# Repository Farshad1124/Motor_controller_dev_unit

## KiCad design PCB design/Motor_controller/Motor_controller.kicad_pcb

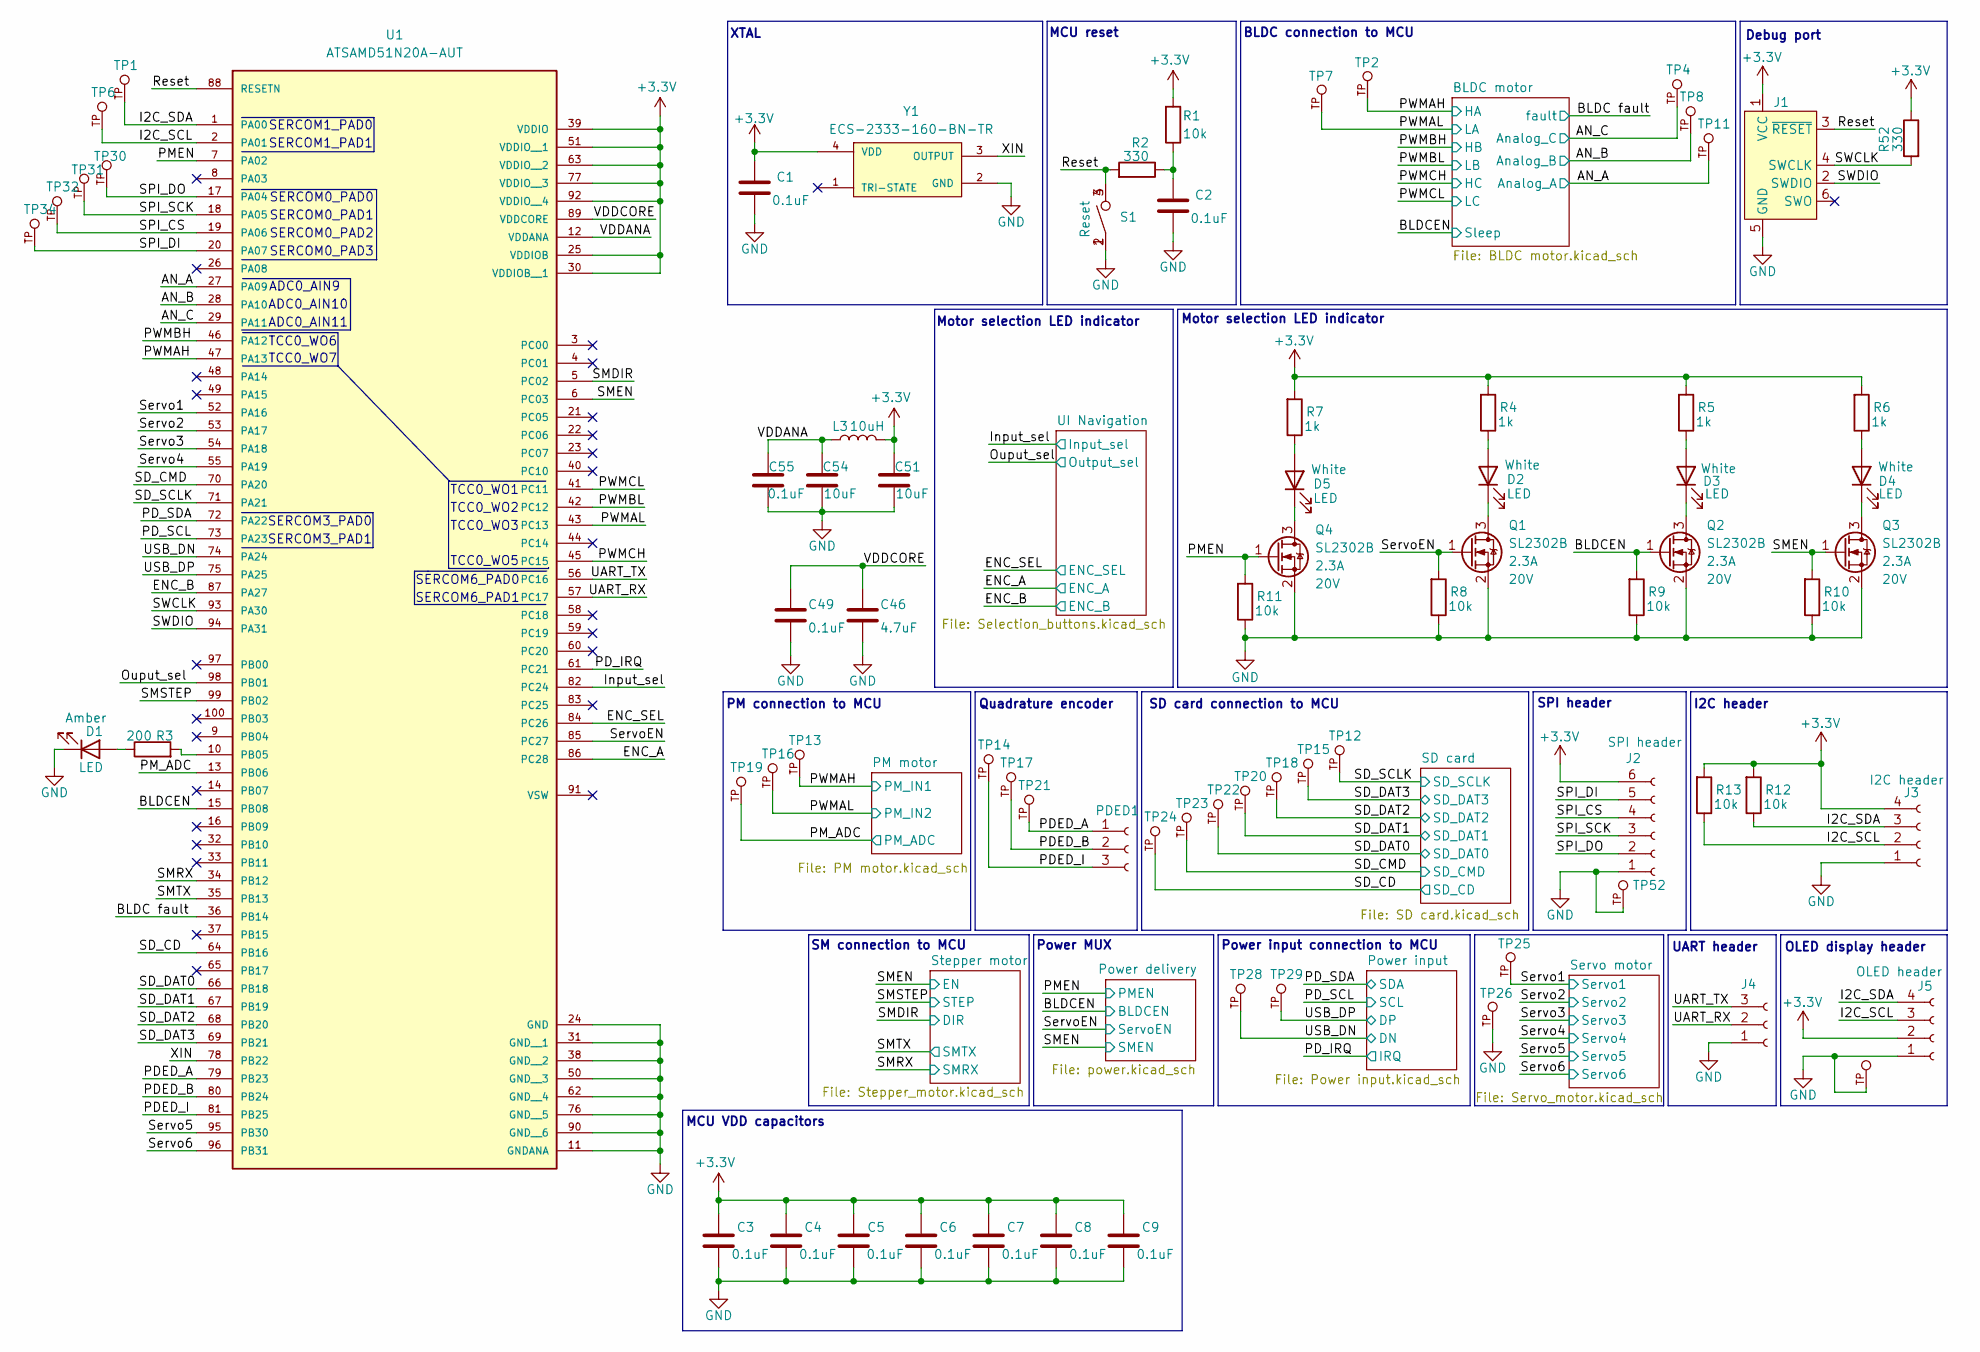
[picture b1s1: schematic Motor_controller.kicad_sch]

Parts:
C1, C2, C3, C4, C5, C6, C7, C8, C9, C49, C55: 0.1uF; C_0603_1608Metric
C46: 4.7uF; C_0603_1608Metric
C51, C54: 10uF; C_0603_1608Metric
D1, D2, D3, D4, D5: LED; LED_0603_1608Metric
J1: Conn_ARM_SWD_TagConnect_TC2030; Tag-Connect_TC2030-IDC-FP_2x03_P1.27mm_Vertical
J2: SPI header; PinSocket_1x06_P2.54mm_Vertical
J3: I2C header; PinSocket_1x04_P2.54mm_Vertical
J4: UART header; PinSocket_1x03_P2.54mm_Vertical
J5: OLED header; PinSocket_1x04_P2.54mm_Vertical
L3: 10uH; L_0805_2012Metric
PDED1: UART header; PinSocket_1x03_P2.54mm_Vertical
Q1, Q2, Q3, Q4: SL2302B; SOT23-3
R1, R8, R9, R10, R11, R12, R13: 10k; R_0603_1608Metric
R2, R52: 330; R_0603_1608Metric
R3: 200; R_0603_1608Metric
R4, R5, R6, R7: 1k; R_0603_1608Metric
S1: Reset; SMT_FS
TP1, TP2, TP4, TP6, TP7, TP8, TP11, TP12, TP13, TP14, TP15, TP16, TP17, TP18, TP19, TP20, TP21, TP22, TP23, TP24, TP25, TP26, TP27, TP28, TP29, TP30, TP31, TP32, TP34, TP52: TestPoint; KEYSTONE_1031; PARTREV B
U1: ATSAMD51N20A-AUT; QFP50P1600X1600X120-100N
Y1: ECS-2333-160-BN-TR; OSC_ECS-2333-160-BN-TR; PARTREV N/A

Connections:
+3.3V: C1.2, C3.2, C4.2, C5.2, C6.2, C7.2, C8.2, C9.2, C51.2, J1.1 (VCC), J2.6, J3.4, J5.2, L3.2, R1.1, R4.1, R5.1, R6.1, R7.1, R12.1, R13.1, R52.2, U1.25 (VDDIOB), U1.30 (VDDIOB__1), U1.39 (VDDIO), U1.51 (VDDIO__1), U1.63 (VDDIO__2), U1.77 (VDDIO__3), U1.92 (VDDIO__4), Y1.4 (VDD); also elsewhere on the board
/AN_A: TP11.TP, U1.27 (PA09); also elsewhere on the board
/AN_B: TP8.TP, U1.28 (PA10); also elsewhere on the board
/AN_C: TP4.TP, U1.29 (PA11); also elsewhere on the board
/BLDC fault: U1.36 (PB14); also elsewhere on the board
/BLDCEN: Q2.1 (G), R9.1, U1.15 (PB08); also elsewhere on the board
/ENC_A: U1.86 (PC28); also elsewhere on the board
/ENC_B: U1.87 (PA27); also elsewhere on the board
/ENC_SEL: U1.84 (PC26); also elsewhere on the board
/I2C_SCL: J3.2, J5.3, R13.2, TP6.TP, U1.2 (PA01)
/I2C_SDA: J3.3, J5.4, R12.2, TP1.TP, U1.1 (PA00)
/Input_sel: U1.82 (PC24); also elsewhere on the board
/Ouput_sel: U1.98 (PB01); also elsewhere on the board
/PDED_A: PDED1.1, TP21.TP, U1.79 (PB23)
/PDED_B: PDED1.2, TP17.TP, U1.80 (PB24)
/PDED_I: PDED1.3, TP14.TP, U1.81 (PB25)
/PD_IRQ: U1.61 (PC21); also elsewhere on the board
/PD_SCL: U1.73 (PA23); also elsewhere on the board
/PD_SDA: U1.72 (PA22); also elsewhere on the board
/PMEN: Q4.1 (G), R11.1, U1.7 (PA02); also elsewhere on the board
/PM_ADC: TP19.TP, U1.13 (PB06); also elsewhere on the board
/PWMAH: TP2.TP, TP13.TP, U1.47 (PA13); also elsewhere on the board
/PWMAL: TP7.TP, TP16.TP, U1.43 (PC13); also elsewhere on the board
/PWMBH: U1.46 (PA12); also elsewhere on the board
/PWMBL: U1.42 (PC12); also elsewhere on the board
/PWMCH: U1.45 (PC15); also elsewhere on the board
/PWMCL: U1.41 (PC11); also elsewhere on the board
/Reset: J1.3 (~RESET), R2.1, S1.3, S1.4, U1.88 (RESETN)
/SD_CD: TP24.TP, U1.64 (PB16); also elsewhere on the board
/SD_CMD: TP23.TP, U1.70 (PA20); also elsewhere on the board
/SD_DAT0: TP22.TP, U1.66 (PB18); also elsewhere on the board
/SD_DAT1: TP20.TP, U1.67 (PB19); also elsewhere on the board
/SD_DAT2: TP18.TP, U1.68 (PB20); also elsewhere on the board
/SD_DAT3: TP15.TP, U1.69 (PB21); also elsewhere on the board
/SD_SCLK: TP12.TP, U1.71 (PA21); also elsewhere on the board
/SMDIR: U1.5 (PC02); also elsewhere on the board
/SMEN: Q3.1 (G), R10.1, U1.6 (PC03); also elsewhere on the board
/SMRX: U1.34 (PB12); also elsewhere on the board
/SMSTEP: U1.99 (PB02); also elsewhere on the board
/SMTX: U1.35 (PB13); also elsewhere on the board
/SPI_CS: J2.4, TP32.TP, U1.19 (PA06)
/SPI_DI: J2.5, TP34.TP, U1.20 (PA07)
/SPI_DO: J2.2, TP30.TP, U1.17 (PA04)
/SPI_SCK: J2.3, TP31.TP, U1.18 (PA05)
/SWCLK: J1.4 (SWCLK), R52.1, U1.93 (PA30)
/SWDIO: J1.2 (SWDIO), U1.94 (PA31)
/Servo1: TP25.TP, U1.52 (PA16); also elsewhere on the board
/Servo2: U1.53 (PA17); also elsewhere on the board
/Servo3: U1.54 (PA18); also elsewhere on the board
/Servo4: U1.55 (PA19); also elsewhere on the board
/Servo5: U1.95 (PB30); also elsewhere on the board
/Servo6: U1.96 (PB31); also elsewhere on the board
/ServoEN: Q1.1 (G), R8.1, U1.85 (PC27); also elsewhere on the board
/UART_RX: J4.2, U1.57 (PC17)
/UART_TX: J4.3, U1.56 (PC16)
/USB_DN: TP28.TP, U1.74 (PA24); also elsewhere on the board
/USB_DP: TP29.TP, U1.75 (PA25); also elsewhere on the board
/VDDANA: C54.2, C55.2, L3.1, U1.12 (VDDANA)
/VDDCORE: C46.2, C49.2, U1.89 (VDDCORE)
/XIN: U1.78 (PB22), Y1.3 (OUTPUT)
GND: C1.1, C2.1, C3.1, C4.1, C5.1, C6.1, C7.1, C8.1, C9.1, C46.1, C49.1, C51.1, C54.1, C55.1, D1.1 (K), J1.5 (GND), J2.1, J3.1, J4.1, J5.1, Q1.2 (S), Q2.2 (S), Q3.2 (S), Q4.2 (S), R8.2, R9.2, R10.2, R11.2, S1.1, S1.2, TP26.TP, TP27.TP, TP52.TP, U1.11 (GNDANA), U1.24 (GND), U1.31 (GND__1), U1.38 (GND__2), U1.50 (GND__3), U1.62 (GND__4), U1.76 (GND__5), U1.90 (GND__6), Y1.2 (GND); also elsewhere on the board
unnamed: C2.2, R1.2, R2.2
unnamed: D1.2 (A), R3.2
unnamed: D2.2 (A), R4.2
unnamed: D2.1 (K), Q1.3 (D)
unnamed: D3.2 (A), R5.2
unnamed: D3.1 (K), Q2.3 (D)
unnamed: D4.2 (A), R6.2
unnamed: D4.1 (K), Q3.3 (D)
unnamed: D5.2 (A), R7.2
unnamed: D5.1 (K), Q4.3 (D)
unnamed: R3.1, U1.10 (PB05)

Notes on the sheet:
Quadrature encoder
OLED display header
SERCOM6_PAD1
Motor selection LED indicator
Power MUX
SERCOM1_PAD1
TCC0_WO6
SERCOM0_PAD2
TCC0_WO7
I2C header
Debug port
SM connection to MCU
SD card connection to MCU
ADC0_AIN9
SERCOM3_PAD0
SERCOM0_PAD0
SERCOM1_PAD0
MCU VDD capacitors
MCU reset
ADC0_AIN11
UART header
PM connection to MCU
SERCOM0_PAD3
XTAL
Power input connection to MCU
ADC0_AIN10
TCC0_WO3
TCC0_WO1
TCC0_WO5
BLDC connection to MCU
SERCOM3_PAD1
SERCOM0_PAD1
SPI header
TCC0_WO2
SERCOM6_PAD0

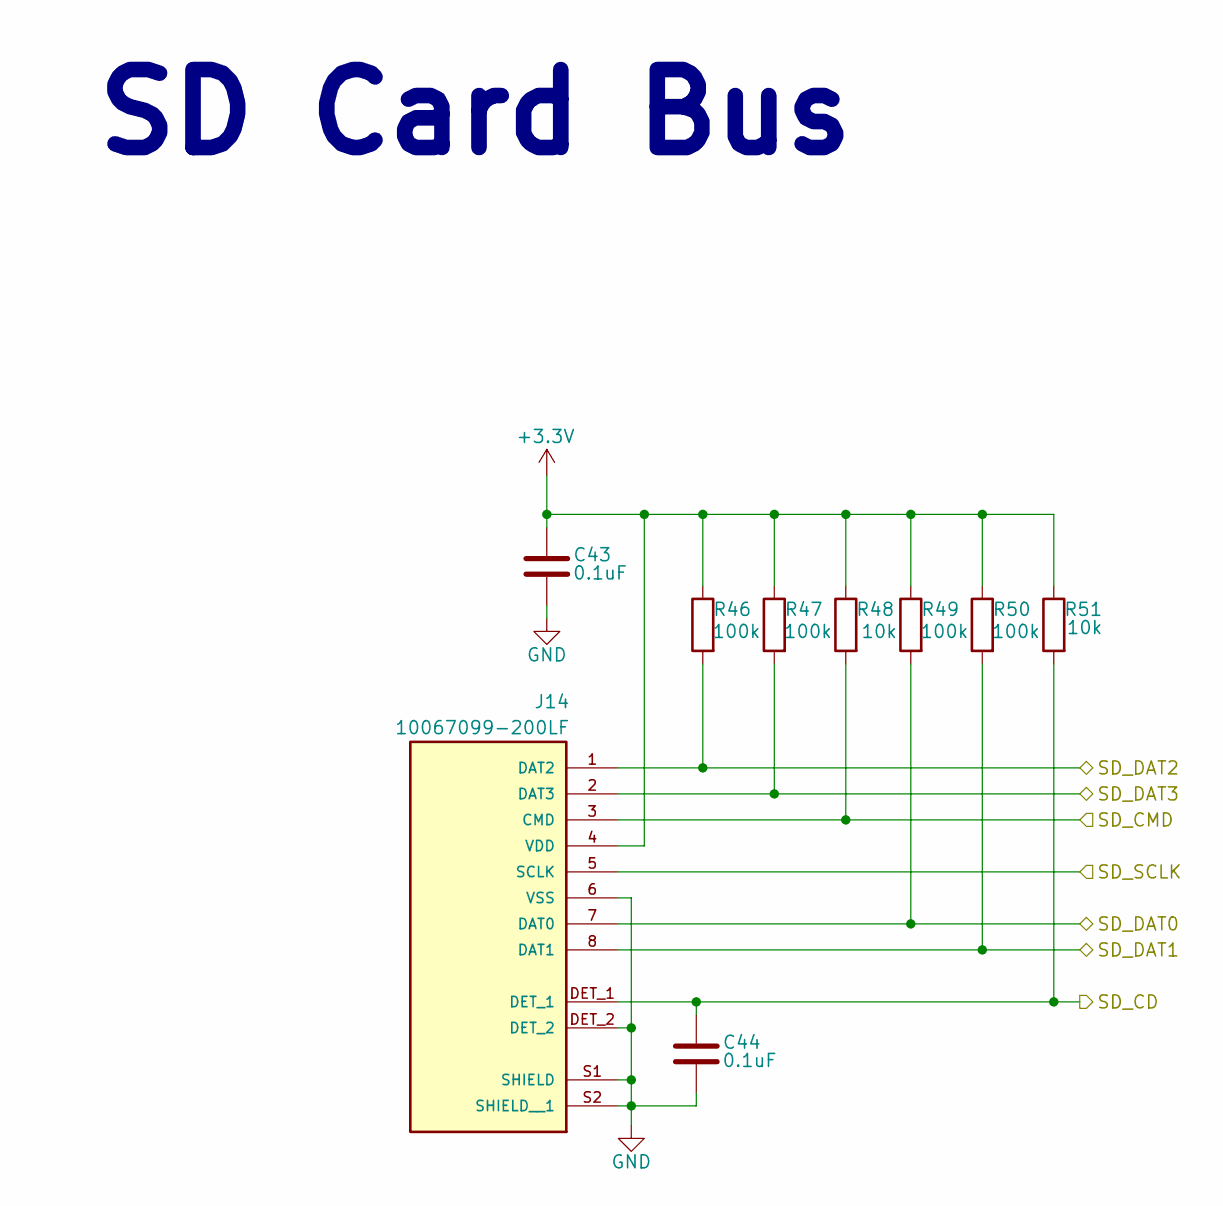
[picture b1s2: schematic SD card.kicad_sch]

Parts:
C43, C44: 0.1uF; C_0603_1608Metric
J14: 10067099-200LF; AMPHENOL_10067099-200LF; PARTREV H
R46, R47, R49, R50: 100k; R_0603_1608Metric
R48, R51: 10k; R_0603_1608Metric

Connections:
+3.3V: C43.2, J14.4 (VDD), R46.2, R47.2, R48.2, R49.2, R50.2, R51.2; also elsewhere on the board
/SD_CD: C44.2, J14.DET_1, R51.1; also elsewhere on the board
/SD_CMD: J14.3 (CMD), R48.1; also elsewhere on the board
/SD_DAT0: J14.7 (DAT0), R49.1; also elsewhere on the board
/SD_DAT1: J14.8 (DAT1), R50.1; also elsewhere on the board
/SD_DAT2: J14.1 (DAT2), R46.1; also elsewhere on the board
/SD_DAT3: J14.2 (DAT3), R47.1; also elsewhere on the board
/SD_SCLK: J14.5 (SCLK); also elsewhere on the board
GND: C43.1, C44.1, J14.6 (VSS), J14.DET_2, J14.S1 (SHIELD), J14.S2 (SHIELD__1); also elsewhere on the board

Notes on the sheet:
SD Card Bus

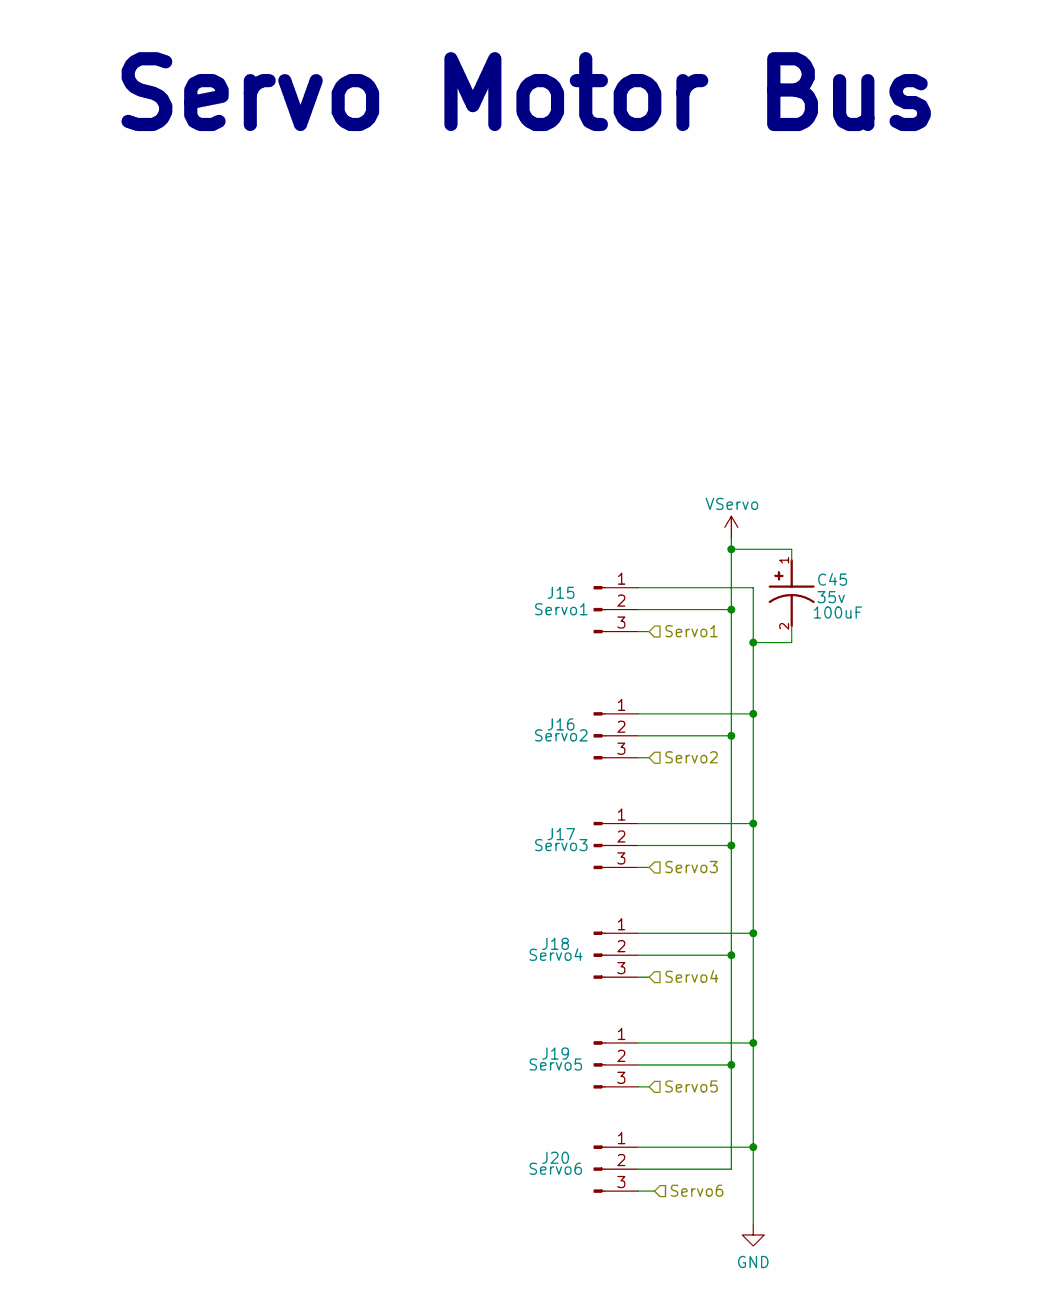
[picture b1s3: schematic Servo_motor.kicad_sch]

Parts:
C45: 100uF; CAPAE660X600N; voltage 35v
J15: Servo1; PinHeader_1x03_P2.54mm_Vertical
J16: Servo2; PinHeader_1x03_P2.54mm_Vertical
J17: Servo3; PinHeader_1x03_P2.54mm_Vertical
J18: Servo4; PinHeader_1x03_P2.54mm_Vertical
J19: Servo5; PinHeader_1x03_P2.54mm_Vertical
J20: Servo6; PinHeader_1x03_P2.54mm_Vertical

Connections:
/Servo1: J15.3; also elsewhere on the board
/Servo2: J16.3; also elsewhere on the board
/Servo3: J17.3; also elsewhere on the board
/Servo4: J18.3; also elsewhere on the board
/Servo5: J19.3; also elsewhere on the board
/Servo6: J20.3; also elsewhere on the board
GND: C45.2, J15.1, J16.1, J17.1, J18.1, J19.1, J20.1; also elsewhere on the board
VServo: C45.1, J15.2, J16.2, J17.2, J18.2, J19.2, J20.2; also elsewhere on the board

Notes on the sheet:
Servo Motor Bus

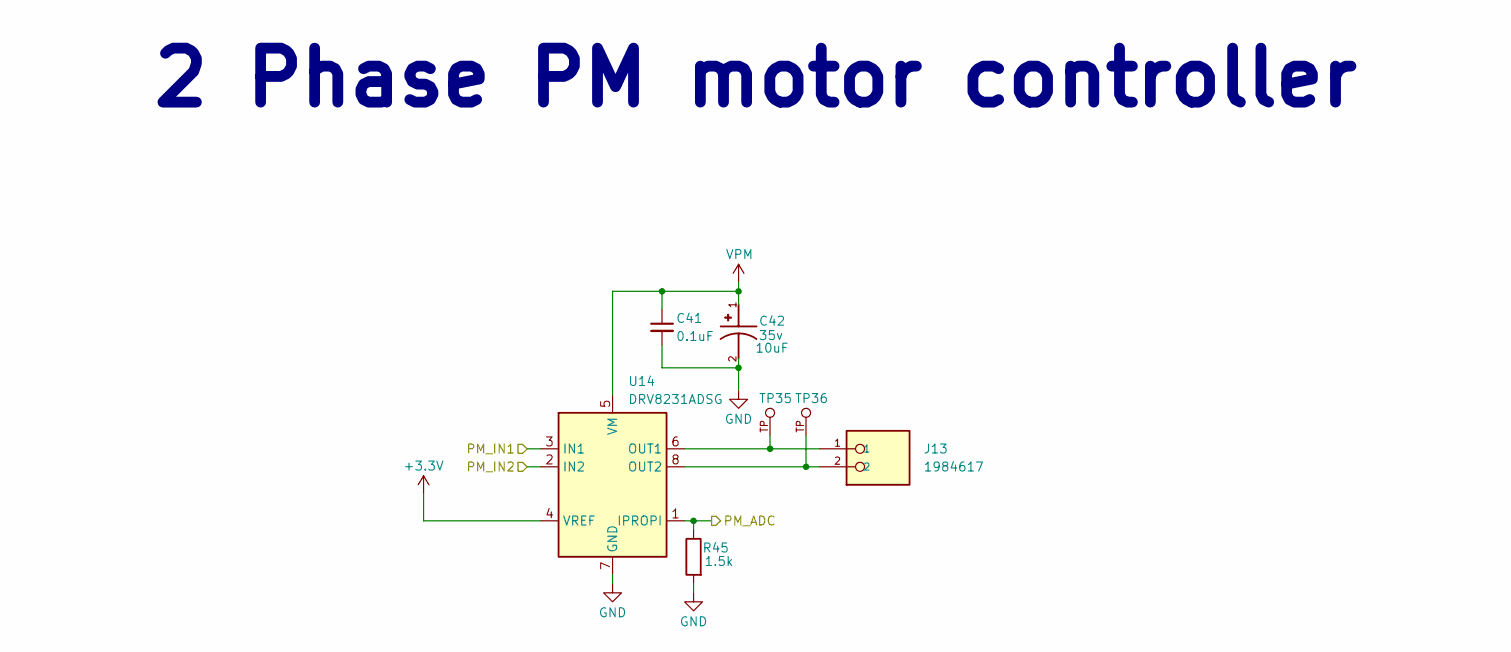
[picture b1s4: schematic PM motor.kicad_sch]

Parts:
C41: 0.1uF; C_0603_1608Metric; voltage 50v
C42: 10uF; CAPAE660X600N; voltage 35v
J13: 1984617; PHOENIX_1984617; PARTREV 22.08.2018
R45: 1.5k; R_0603_1608Metric
TP35, TP36: TestPoint; KEYSTONE_1031; PARTREV B
U14: DRV8231ADSG; WSON8_DSG_TEX

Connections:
+3.3V: U14.4 (VREF); also elsewhere on the board
/PM_ADC: R45.2, U14.1 (IPROPI); also elsewhere on the board
/PWMAH: U14.3 (IN1); also elsewhere on the board
/PWMAL: U14.2 (IN2); also elsewhere on the board
GND: C41.2, C42.2, R45.1, U14.7 (GND), U14.9 (GND); also elsewhere on the board
unnamed: J13.1, TP35.TP, U14.6 (OUT1)
unnamed: J13.2, TP36.TP, U14.8 (OUT2)
VPM: C41.1, C42.1, U14.5 (VM); also elsewhere on the board

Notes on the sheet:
2 Phase PM motor controller

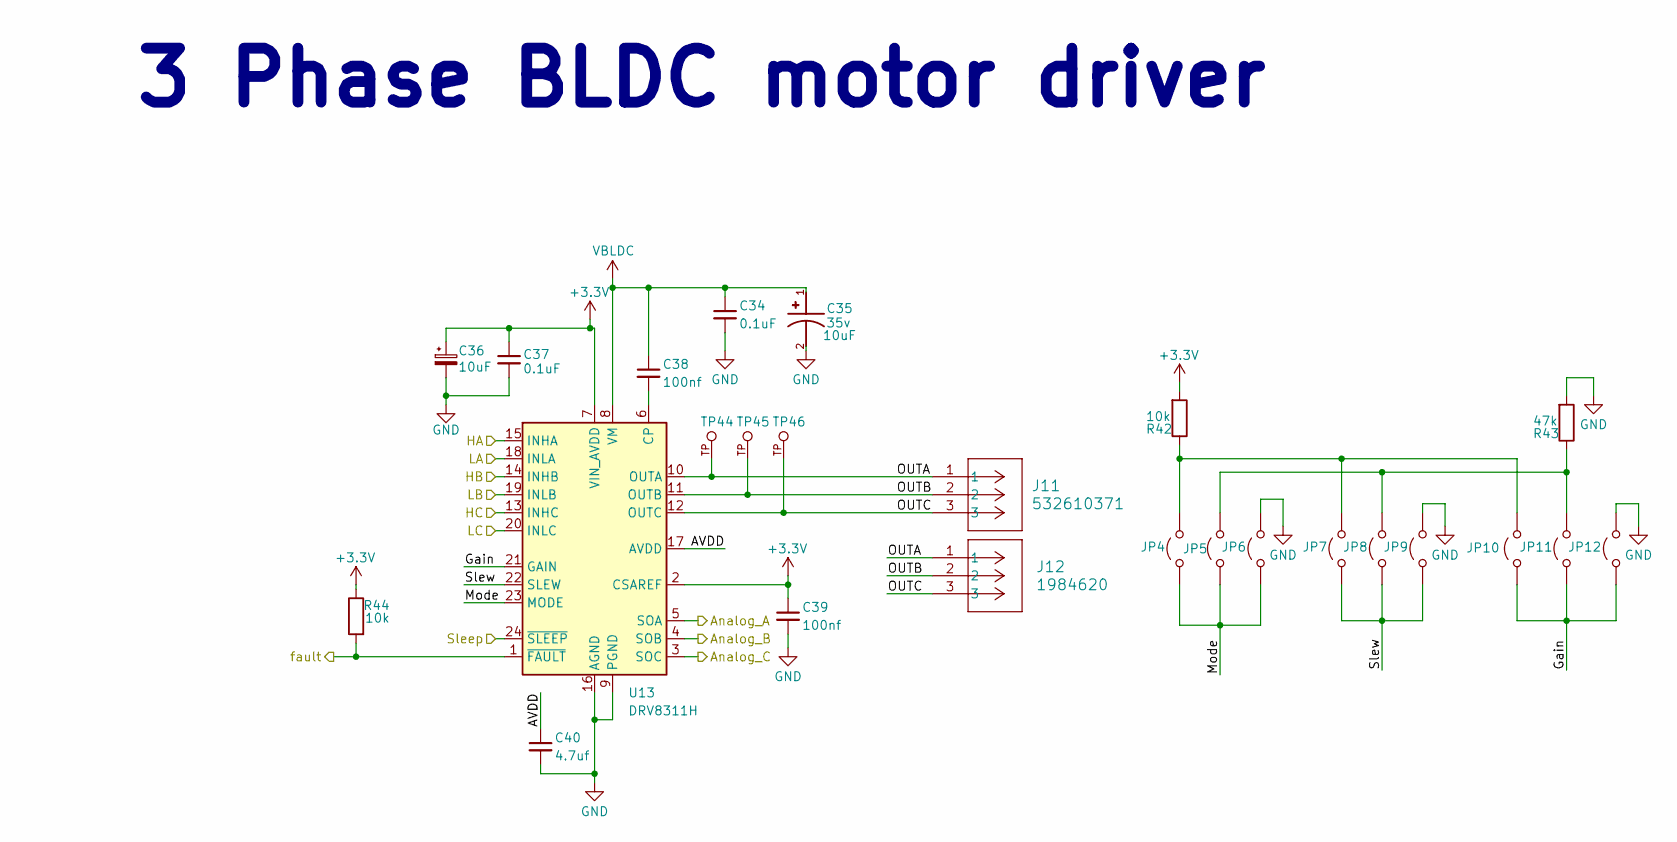
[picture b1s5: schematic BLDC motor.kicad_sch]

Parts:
C34, C37: 0.1uF; C_0603_1608Metric
C35: 10uF; CAPAE660X600N; voltage 35v
C36: 10uF; CP_EIA-2012-12_Kemet-R
C38, C39: 100nf; C_0603_1608Metric; voltage 50v
C40: 4.7uf; C_0603_1608Metric
J11: 532610371; CONN_532610001-SD_03_MOL
J12: 1984620; CONN_1984620_PXC
JP4, JP5, JP6, JP7, JP8, JP9, JP10, JP11, JP12: NPC02SXON-RC; TestPoint_2Pads_Pitch2.54mm_Drill0.8mm
R42, R44: 10k; R_0603_1608Metric
R43: 47k; R_0603_1608Metric
TP44, TP45, TP46: TestPoint; KEYSTONE_1031; PARTREV B
U13: DRV8311H; Texas_RRW0024A_WQFN-24-1EP_3x3mm_P0.4mm_EP1.9x1.9mm_Thermal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

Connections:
+3.3V: C36.1, C37.1, C39.1, R42.1, R44.2, U13.2 (CSAREF), U13.7 (VIN_AVDD); also elsewhere on the board
/AN_A: U13.5 (SOA); also elsewhere on the board
/AN_B: U13.4 (SOB); also elsewhere on the board
/AN_C: U13.3 (SOC); also elsewhere on the board
/BLDC fault: R44.1, U13.1 (~FAULT); also elsewhere on the board
/BLDC motor/AVDD: C40.1, U13.17 (AVDD)
/BLDC motor/Gain: JP10.1 (A), JP11.1 (A), JP12.1 (A), U13.21 (GAIN)
/BLDC motor/Mode: JP4.1 (A), JP5.1 (A), JP6.1 (A), U13.23 (MODE)
/BLDC motor/OUTA: J11.1, J12.1, TP44.TP, U13.10 (OUTA)
/BLDC motor/OUTB: J11.2, J12.2, TP45.TP, U13.11 (OUTB)
/BLDC motor/OUTC: J11.3, J12.3, TP46.TP, U13.12 (OUTC)
/BLDC motor/Slew: JP7.1 (A), JP8.1 (A), JP9.1 (A), U13.22 (SLEW)
/BLDCEN: U13.24 (~SLEEP); also elsewhere on the board
/PWMAH: U13.15 (INHA); also elsewhere on the board
/PWMAL: U13.18 (INLA); also elsewhere on the board
/PWMBH: U13.14 (INHB); also elsewhere on the board
/PWMBL: U13.19 (INLB); also elsewhere on the board
/PWMCH: U13.13 (INHC); also elsewhere on the board
/PWMCL: U13.20 (INLC); also elsewhere on the board
GND: C34.2, C35.2, C36.2, C37.2, C39.2, C40.2, JP6.2 (B), JP9.2 (B), JP12.2 (B), R43.1, U13.9 (PGND), U13.16 (AGND), U13.25 (PGND); also elsewhere on the board
unnamed: JP4.2 (B), JP7.2 (B), JP10.2 (B), R42.2
unnamed: JP5.2 (B), JP8.2 (B), JP11.2 (B), R43.2
unnamed: C38.2, U13.6 (CP)
VBLDC: C34.1, C35.1, C38.1, U13.8 (VM); also elsewhere on the board

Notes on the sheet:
3 Phase BLDC motor driver

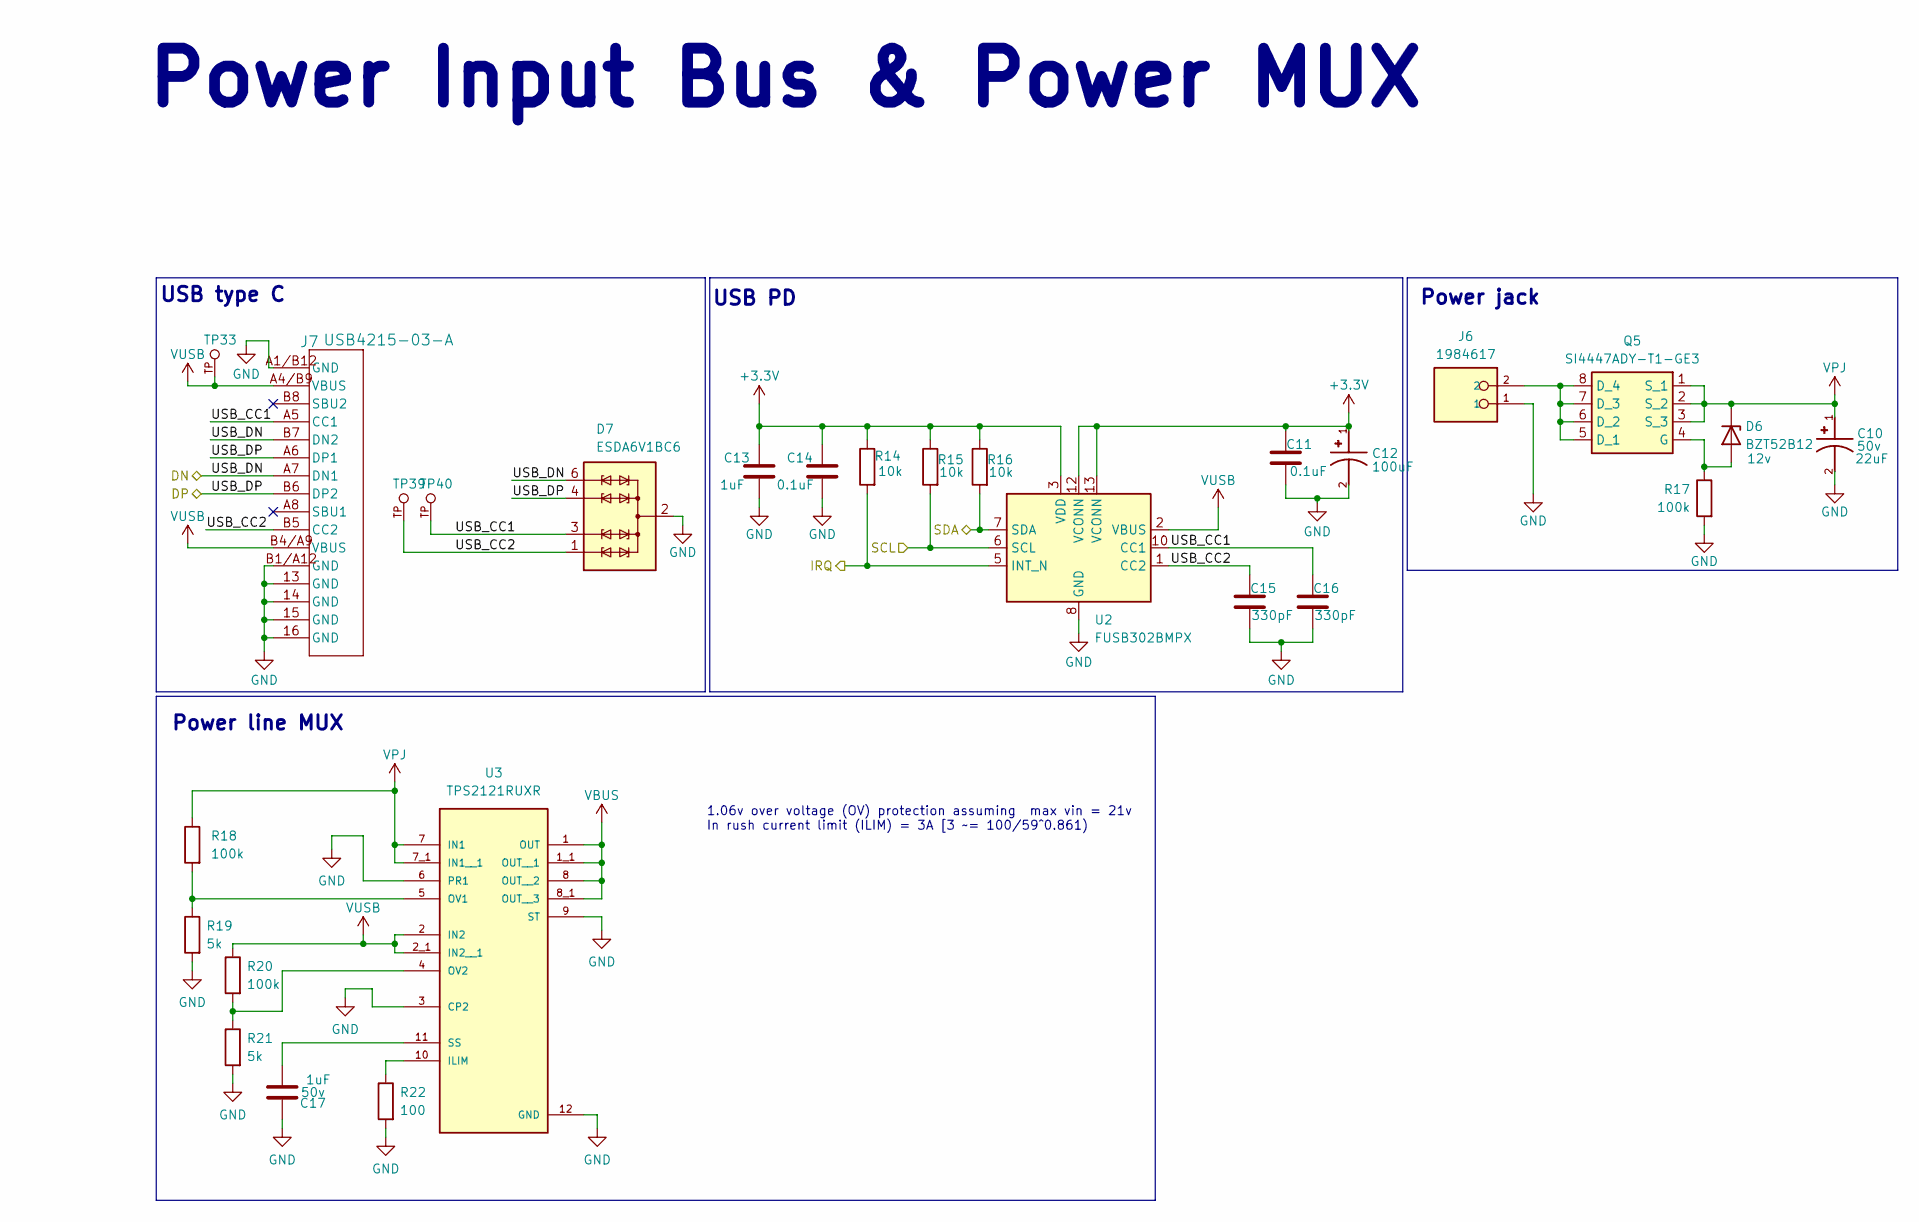
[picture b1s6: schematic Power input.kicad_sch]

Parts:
C10: 22uF; CAPAE660X600N; voltage 50v
C11, C14: 0.1uF; C_0603_1608Metric
C12: 100uF; CP_EIA-3528-12_Kemet-T; voltage 50v
C13: 1uF; C_0603_1608Metric
C15, C16: 330pF; C_0603_1608Metric
C17: 1uF; C_0603_1608Metric; Voltage 50v
D6: BZT52B12; D_SOD-123; voltage 12v
D7: ESDA6V1BC6; SOT-23-6
J6: 1984617; PHOENIX_1984617; PARTREV 22.08.2018
J7: USB4215-03-A; USBC_CONN_8p94X6p5X3p16_12L_GCC
Q5: SI4447ADY-T1-GE3; SOIC127P600X175-8N; Mouser Part Number 78-SI4447ADY-T1-GE3
R14, R15, R16: 10k; R_0603_1608Metric
R17, R18, R20: 100k; R_0603_1608Metric
R19, R21: 5k; R_0603_1608Metric
R22: 100; R_0603_1608Metric
TP33, TP39, TP40: TestPoint; KEYSTONE_1031; PARTREV B
U2: FUSB302BMPX; WQFN-14-1EP_2.5x2.5mm_P0.5mm_EP1.45x1.45mm
U3: TPS2121RUXR; IC_TPS2121RUXR

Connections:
+3.3V: C11.2, C12.1, C13.2, C14.2, R14.2, R15.2, R16.2, U2.3 (VDD), U2.4 (VDD), U2.12 (VCONN), U2.13 (VCONN); also elsewhere on the board
/PD_IRQ: R14.1, U2.5 (INT_N); also elsewhere on the board
/PD_SCL: R15.1, U2.6 (SCL); also elsewhere on the board
/PD_SDA: R16.1, U2.7 (SDA); also elsewhere on the board
/Power input/USB_CC1: C16.2, D7.3 (TVS2), J7.A5 (CC1), TP40.TP, U2.10 (CC1), U2.11 (CC1)
/Power input/USB_CC2: C15.2, D7.1 (TVS1), J7.B5 (CC2), TP39.TP, U2.1 (CC2), U2.14 (CC2)
/USB_DN: D7.6 (TVS4), J7.A7 (DN1), J7.B7 (DN2); also elsewhere on the board
/USB_DP: D7.4 (TVS3), J7.A6 (DP1), J7.B6 (DP2); also elsewhere on the board
GND: C10.2, C11.1, C12.2, C13.1, C14.1, C15.1, C16.1, C17.2, D7.2 (COM), D7.5 (COM), J6.1, J7.13 (GND), J7.14 (GND), J7.15 (GND), J7.16 (GND), J7.A1/B12 (GND), J7.B1/A12 (GND), R17.2, R19.2, R21.2, R22.2, U2.8 (GND), U2.9 (GND), U2.15 (GND), U3.3 (CP2), U3.6 (PR1), U3.9 (ST), U3.12 (GND); also elsewhere on the board
unnamed: D6.2 (A), Q5.4 (G), R17.1
unnamed: J6.2, Q5.5 (D_1), Q5.6 (D_2), Q5.7 (D_3), Q5.8 (D_4)
unnamed: R22.1, U3.10 (ILIM)
unnamed: R18.2, R19.1, U3.5 (OV1)
unnamed: R20.2, R21.1, U3.4 (OV2)
unnamed: C17.1, U3.11 (SS)
VBUS: U3.1 (OUT), U3.1_1 (OUT__1), U3.8 (OUT__2), U3.8_1 (OUT__3); also elsewhere on the board
VPJ: C10.1, D6.1 (K), Q5.1 (S_1), Q5.2 (S_2), Q5.3 (S_3), R18.1, U3.7 (IN1), U3.7_1 (IN1__1)
VUSB: J7.A4/B9 (VBUS), J7.B4/A9 (VBUS), R20.1, TP33.TP, U2.2 (VBUS), U3.2 (IN2), U3.2_1 (IN2__1)

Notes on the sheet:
Power Input Bus & Power MUX
USB PD
USB type C
Power line MUX
1.06v over voltage (OV) protection assuming max vin = 21v In rush current limit (ILIM) = 3A [3 ~= 100/59^0.861)
Power jack

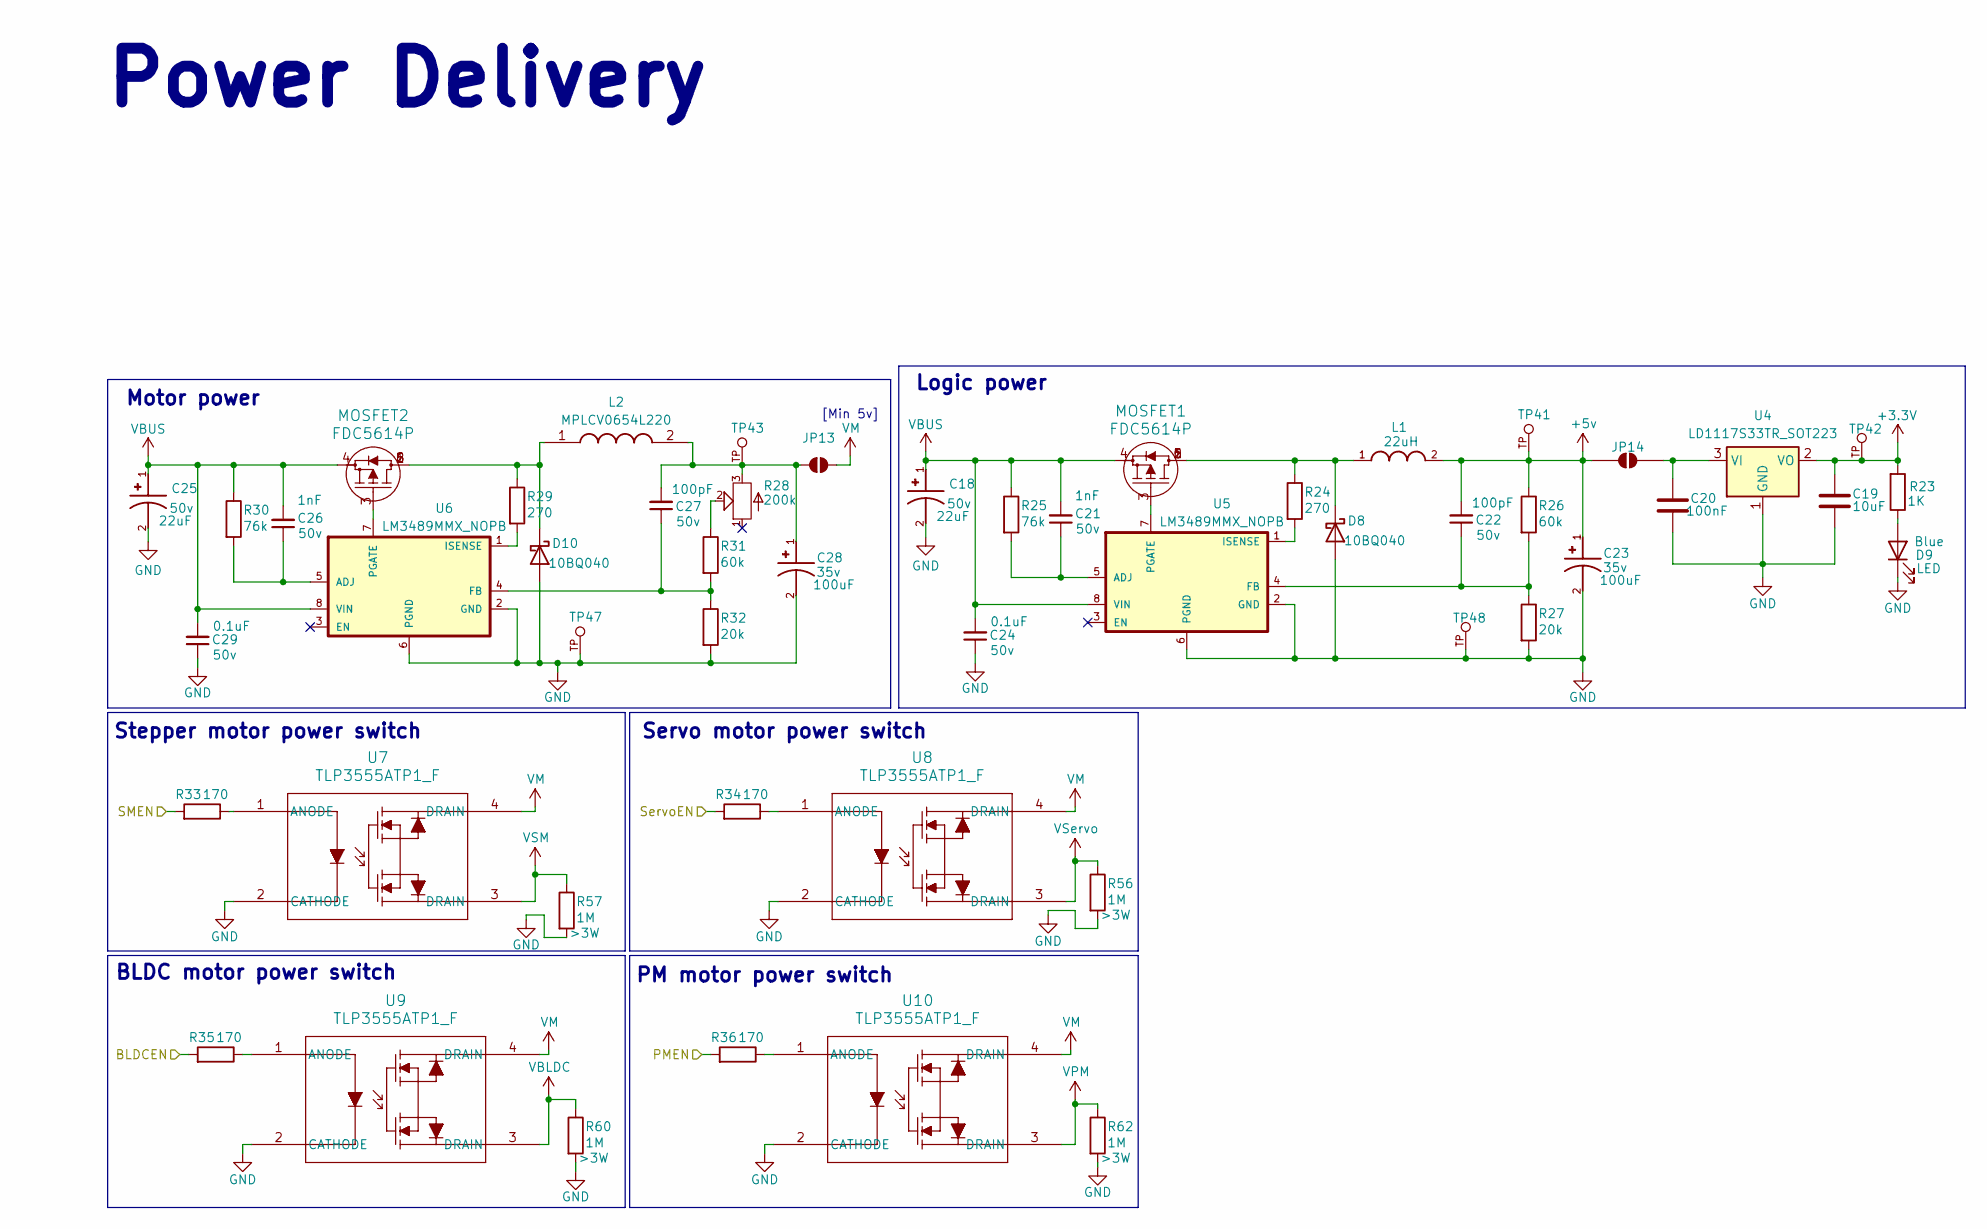
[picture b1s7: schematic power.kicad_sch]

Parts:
C18, C25: 22uF; CAPAE660X600N; voltage 50v
C19: 10uF; C_0603_1608Metric
C20: 100nF; C_0603_1608Metric
C21, C26: 1nF; C_0603_1608Metric; Voltage 50v
C22, C27: 100pF; C_0603_1608Metric; Voltage 50v
C23, C28: 100uF; CAPAE660X600N; voltage 35v
C24, C29: 0.1uF; C_0603_1608Metric; Voltage 50v
D8, D10: 10BQ040; D_SMB
D9: LED; LED_0603_1608Metric
JP13: Jumper_2_NO
JP14: SolderJumper_2_Open; SolderJumper-2_P1.3mm_Open_RoundedPad1.0x1.5mm
L1: 22uH; IND_VLS6045EX-220M
L2: MPLCV0654L220; INDPM7967X540N; Mouser Part Number 80-MPLCV0654L220
MOSFET1, MOSFET2: FDC5614P; TSOT23-6_419BL_ONS
R23: 1K; R_0603_1608Metric
R24, R29: 270; R_0603_1608Metric
R25, R30: 76k; R_0603_1608Metric
R26, R31: 60k; R_0603_1608Metric
R27, R32: 20k; R_0603_1608Metric
R28: 200k; TRIM_TC33X-2-204E
R33, R34, R35, R36: 170; R_0603_1608Metric
R56, R57, R60, R62: 1M; R_1206_3216Metric
TP41, TP42, TP43, TP47, TP48: TestPoint; KEYSTONE_1031; PARTREV B
U4: LD1117S33TR_SOT223; SOT-223-3_TabPin2
U5, U6: LM3489MMX_NOPB; SOP65P490X110-8N
U7, U8, U9, U10: TLP3555ATP1_F; 11-5B201S_TOS

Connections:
+3.3V: C19.2, R23.1, TP42.TP, U4.2 (VO); also elsewhere on the board
+5v: C22.2, C23.1, JP14.2 (B), L1.2, R26.1, TP41.TP
/BLDCEN: R35.1; also elsewhere on the board
/PMEN: R36.1; also elsewhere on the board
/SMEN: R33.1; also elsewhere on the board
/ServoEN: R34.1; also elsewhere on the board
GND: C18.2, C19.1, C20.1, C23.2, C24.1, C25.2, C28.2, C29.1, D8.2 (A), D9.1 (K), D10.2 (A), R27.2, R32.2, R56.2, R57.2, R60.2, R62.2, TP47.TP, TP48.TP, U4.1 (GND), U5.2 (GND), U5.6 (PGND), U6.2 (GND), U6.6 (PGND), U7.2 (CATHODE), U8.2 (CATHODE), U9.2 (CATHODE), U10.2 (CATHODE); also elsewhere on the board
unnamed: D8.1 (K), L1.1, MOSFET1.1, MOSFET1.2, MOSFET1.5, MOSFET1.6, R24.1
unnamed: D9.2 (A), R23.2
unnamed: D10.1 (K), L2.1, MOSFET2.1, MOSFET2.2, MOSFET2.5, MOSFET2.6, R29.1
unnamed: C27.2, C28.1, JP13.2 (B), L2.2, R28.3, TP43.TP
unnamed: C20.2, JP14.1 (A), U4.3 (VI)
unnamed: R28.2, R31.1
unnamed: C21.1, R25.2, U5.5 (ADJ)
unnamed: C22.1, R26.2, R27.1, U5.4 (FB)
unnamed: R24.2, U5.1 (ISENSE)
unnamed: MOSFET1.3, U5.7 (PGATE)
unnamed: C26.1, R30.2, U6.5 (ADJ)
unnamed: C27.1, R31.2, R32.1, U6.4 (FB)
unnamed: R29.2, U6.1 (ISENSE)
unnamed: MOSFET2.3, U6.7 (PGATE)
unnamed: R33.2, U7.1 (ANODE)
unnamed: R34.2, U8.1 (ANODE)
unnamed: R35.2, U9.1 (ANODE)
unnamed: R36.2, U10.1 (ANODE)
VBLDC: R60.1, U9.3 (DRAIN); also elsewhere on the board
VBUS: C18.1, C21.2, C24.2, C25.1, C26.2, C29.2, MOSFET1.4, MOSFET2.4, R25.1, R30.1, U5.8 (VIN), U6.8 (VIN); also elsewhere on the board
VM: JP13.1 (A), U7.4 (DRAIN), U8.4 (DRAIN), U9.4 (DRAIN), U10.4 (DRAIN)
VPM: R62.1, U10.3 (DRAIN); also elsewhere on the board
VSM: R57.1, U7.3 (DRAIN); also elsewhere on the board
VServo: R56.1, U8.3 (DRAIN); also elsewhere on the board

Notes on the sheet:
[Min 5v]
Logic power
Servo motor power switch
Motor power
PM motor power switch
Stepper motor power switch
Power Delivery
BLDC motor power switch
